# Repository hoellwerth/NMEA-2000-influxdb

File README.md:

# NMEA-2000-influxdb
An esp32 which posts traffic in the NMEA 2000 BUS to an InfluxDB 2.7 instance.

## Table of contents

- [Electrical](/Electrical): A KiCad project
- [Mechanical](/Mechanical): 3D files for casing etc.
- [Software](/Software): Platform IO Files

## Features

- [x] Listen for all known PGNs
- [x] Post data to an InfluxDB 2.7 instance
- [x] Save data to an SD-Card while offline 
- [ ] Use wifimanager

## Contribution

If you want to help with a feature or add something, just fork the repository, make your changes and open a Pull Request

## License

This project ist licensed under the [GNU GENERAL PUBLIC LICENSE](/LICENSE)

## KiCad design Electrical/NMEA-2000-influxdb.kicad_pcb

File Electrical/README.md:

# Electrical

## Table of Contents
- [Electrical](https://github.com/hoellwerth/NMEA-2000-influxdb/tree/master/Electrical#electrical)
  - [Schematic](https://github.com/hoellwerth/NMEA-2000-influxdb/blob/master/Electrical/production/schematic.pdf) The KiCad Schematic

## Components-List

A list of all the electrical components I used for the project:

- ESP32-WROOM-32E
- CAN-Transeiver SN65HVD230
- SD-Card Slot
- LM7805
- AMS1117
- BME280

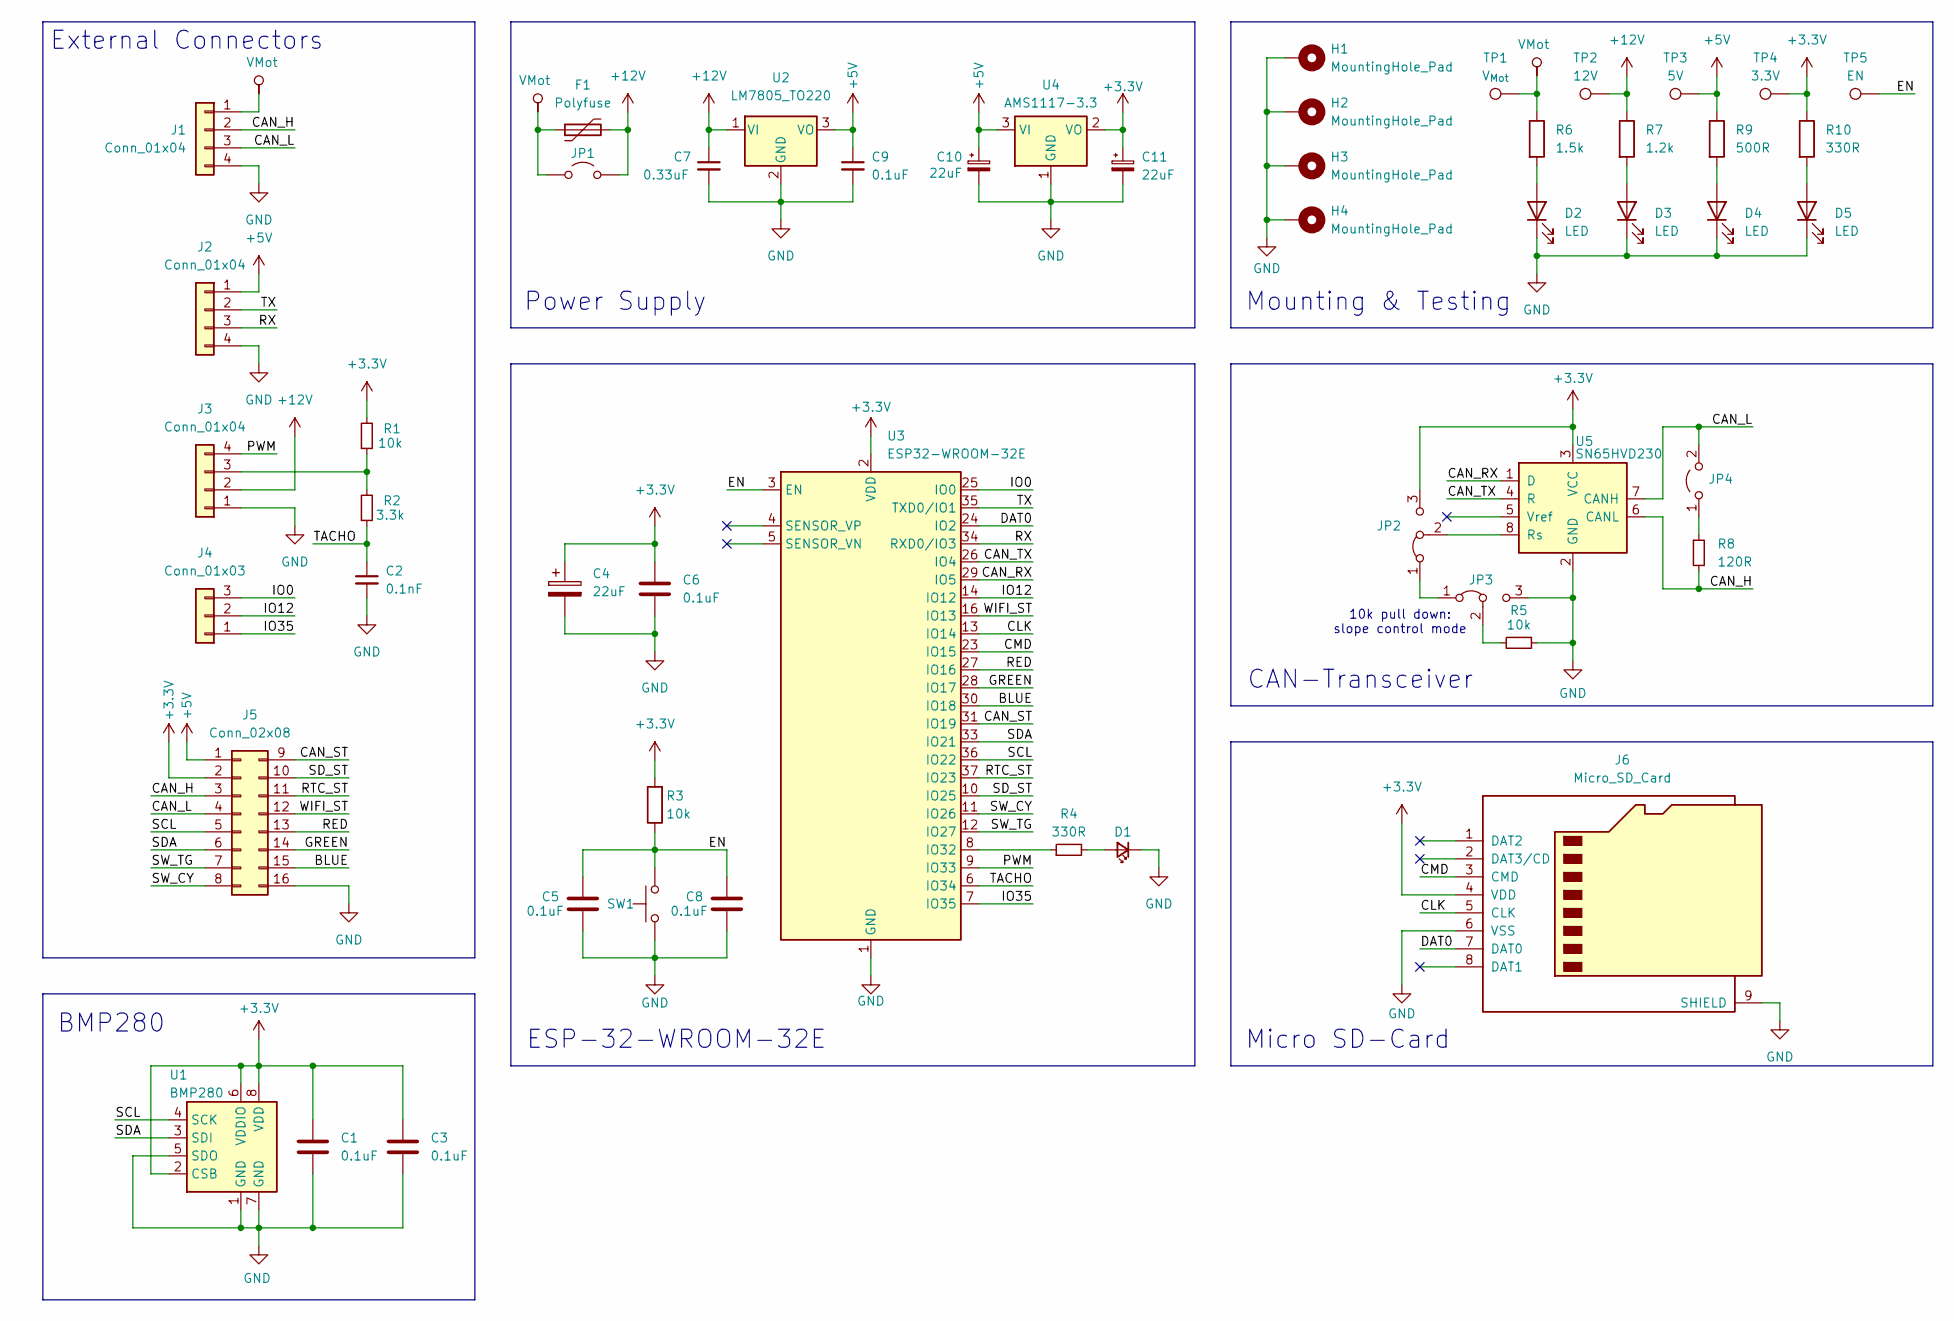
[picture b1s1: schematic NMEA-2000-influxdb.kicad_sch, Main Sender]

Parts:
C1, C3, C5, C6, C8, C9: 0.1uF; C_Disc_D5.0mm_W2.5mm_P5.00mm
C2: 0.1nF; C_Disc_D5.0mm_W2.5mm_P5.00mm
C4, C10, C11: 22uF; C_Radial_D4.0mm_H7.0mm_P1.50mm
C7: 0.33uF; C_Disc_D5.0mm_W2.5mm_P5.00mm
D1: LED_Small; LED_D3.0mm
D2, D3, D4, D5: LED; LED_D3.0mm
F1: Polyfuse; D_1210_3225Metric_Pad1.42x2.65mm_HandSolder
H1, H2, H3, H4: MountingHole_Pad; MountingHole_3mm_Pad_Via
J1: Conn_01x04; TerminalBlock_Phoenix_PT-1,5-4-5.0-H_1x04_P5.00mm_Horizontal
J2: Conn_01x04; PinSocket_1x04_P2.54mm_Horizontal
J3: Conn_01x04; FanPinHeader_1x04_P2.54mm_Vertical
J4: Conn_01x03; PinHeader_1x03_P2.54mm_Vertical
J5: Conn_02x08; IDC-Header_2x08_P2.54mm_Vertical
J6: Micro_SD_Card; microSD_HC_Hirose_DM3AT-SF-PEJM5
JP1, JP4: Jumper_2_Open; PinHeader_1x02_P2.54mm_Vertical
JP2, JP3: Jumper_3_Bridged12; PinHeader_1x03_P2.54mm_Vertical
R1, R3, R5: 10k; R_Axial_DIN0207_L6.3mm_D2.5mm_P10.16mm_Horizontal
R2: 3.3k; R_Axial_DIN0207_L6.3mm_D2.5mm_P10.16mm_Horizontal
R4, R10: 330R; R_Axial_DIN0207_L6.3mm_D2.5mm_P10.16mm_Horizontal
R6: 1.5k; R_Axial_DIN0207_L6.3mm_D2.5mm_P10.16mm_Horizontal
R7: 1.2k; R_Axial_DIN0207_L6.3mm_D2.5mm_P10.16mm_Horizontal
R8: 120R; R_Axial_DIN0207_L6.3mm_D2.5mm_P10.16mm_Horizontal
R9: 500R; R_Axial_DIN0207_L6.3mm_D2.5mm_P10.16mm_Horizontal
SW1: SW_Push; SW_PUSH_6mm
TP1: V_{Mot}; TestPoint_Pad_2.5x2.5mm
TP2: 12V; TestPoint_Pad_2.5x2.5mm
TP3: 5V; TestPoint_Pad_2.5x2.5mm
TP4: 3.3V; TestPoint_Pad_2.5x2.5mm
TP5: EN; TestPoint_Pad_2.5x2.5mm
U1: BMP280; Bosch_LGA-8_2x2.5mm_P0.65mm_ClockwisePinNumbering
U2: LM7805_TO220; TO-220-3_Vertical
U3: ESP32-WROOM-32E; ESP32-WROOM-32D
U4: AMS1117-3.3; SOT-223-3_TabPin2
U5: SN65HVD230; SOIC-8_3.9x4.9mm_P1.27mm

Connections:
+3.3V: C1.1, C3.1, C4.1, C6.1, C11.1, J5.2, J6.4 (VDD), JP2.3 (B), R1.2, R3.2, R10.1, TP4.1, U1.2 (CSB), U1.6 (VDDIO), U1.8 (VDD), U3.2 (VDD), U4.2 (VO), U5.3 (VCC)
+5V: C9.1, C10.1, J2.1, J5.1, R9.1, TP3.1, U2.3 (VO), U4.3 (VI)
+12V: C7.1, F1.2, J3.2, JP1.2 (B), R7.1, TP2.1, U2.1 (VI)
/BLUE: J5.15, U3.30 (IO18)
/CAN_H: J1.2, J5.3, R8.2, U5.6 (CANL)
/CAN_L: J1.3, J5.4, JP4.2 (B), U5.7 (CANH)
/CAN_RX: U3.29 (IO5), U5.1 (D)
/CAN_ST: J5.9, U3.31 (IO19)
/CAN_TX: U3.26 (IO4), U5.4 (R)
/CLK: J6.5 (CLK), U3.13 (IO14)
/CMD: J6.3 (CMD), U3.23 (IO15)
/DAT0: J6.7 (DAT0), U3.24 (IO2)
/EN: C5.2, C8.2, R3.1, SW1.2, TP5.1, U3.3 (EN)
/GREEN: J5.14, U3.28 (IO17)
/IO0: J4.3, U3.25 (IO0)
/IO12: J4.2, U3.14 (IO12)
/IO35: J4.1, U3.7 (IO35)
/PWM: J3.4, U3.9 (IO33)
/RED: J5.13, U3.27 (IO16)
/RTC_ST: J5.11, U3.37 (IO23)
/RX: J2.3, U3.34 (RXD0/IO3)
/SCL: J5.5, U1.4 (SCK), U3.36 (IO22)
/SDA: J5.6, U1.3 (SDI), U3.33 (IO21)
/SD_ST: J5.10, U3.10 (IO25)
/SW_CY: J5.8, U3.11 (IO26)
/SW_TG: J5.7, U3.12 (IO27)
/TACHO: C2.1, R2.1, U3.6 (IO34)
/TX: J2.2, U3.35 (TXD0/IO1)
/WIFI_ST: J5.12, U3.16 (IO13)
GND: C1.2, C2.2, C3.2, C4.2, C5.1, C6.2, C7.2, C8.1, C9.2, C10.2, C11.2, D1.1 (K), D2.1 (K), D3.1 (K), D4.1 (K), D5.1 (K), H1.1, H2.1, H3.1, H4.1, J1.4, J2.4, J3.1, J5.16, J6.6 (VSS), J6.9 (SHIELD), JP3.3 (B), R5.1, SW1.1, U1.1 (GND), U1.5 (SDO), U1.7 (GND), U2.2 (GND), U3.1 (GND), U3.15 (GND), U3.38 (GND), U3.39 (GND), U4.1 (GND), U5.2 (GND)
unnamed: D1.2 (A), R4.2
unnamed: D2.2 (A), R6.2
unnamed: D3.2 (A), R7.2
unnamed: D4.2 (A), R9.2
unnamed: D5.2 (A), R10.2
unnamed: J3.3, R1.1, R2.2
unnamed: JP2.1 (A), JP3.1 (A)
unnamed: JP2.2 (C), U5.8 (Rs)
unnamed: JP3.2 (C), R5.2
unnamed: JP4.1 (A), R8.1
unnamed: R4.1, U3.8 (IO32)
VMot: F1.1, J1.1, JP1.1 (A), R6.1, TP1.1

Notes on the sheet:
Power Supply
CAN-Transceiver
Mounting & Testing
ESP-32-WROOM-32E
10k pull down: slope control mode
Micro SD-Card
BMP280
External Connectors

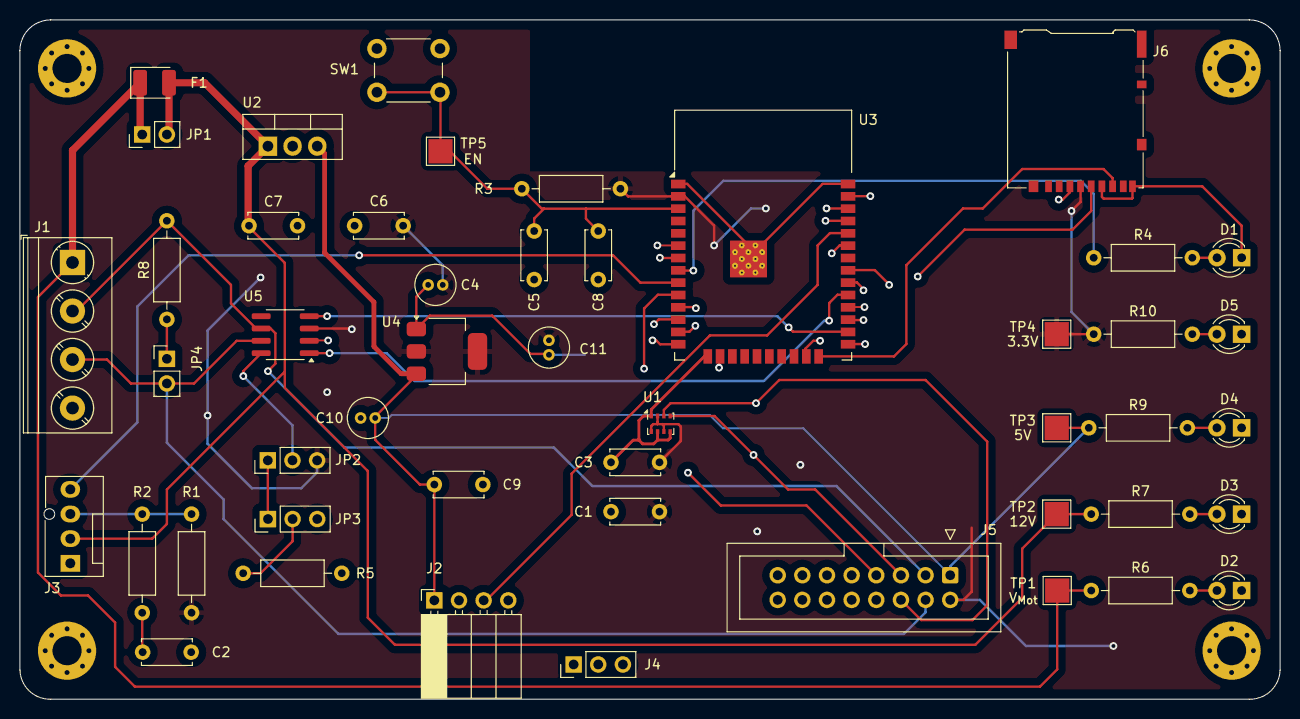
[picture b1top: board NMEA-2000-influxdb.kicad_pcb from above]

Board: 4 copper layers, 129.9 x 70.0 mm, 52 parts (0 on the bottom side), 42 nets.

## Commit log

2023-05-15 Added Arduino script
2023-05-15 Added KiCad Project
2023-05-15 Added KiCad Schematic
2023-05-15 Added KiCad PCB
2023-05-20 Added InfluxDB Write
2023-06-04 Added Receiver
2023-06-04 Updated Receiver
2023-06-04 Changed too much
2023-06-05 Added BatterHandler
2023-06-06 Updated connection validation
2023-06-06 Added TymeSync
2023-06-06 Added connectWifi
2023-06-08 Added Voltage to Influx
2023-06-09 Added Current and Temp to Influx
2023-06-09 Added handleFluidTanks
2023-06-11 Updated KiCad Project
2023-06-11 Updated KiCad Schematic
2023-06-12 Moved KiCad project into 'Electrical' Folder
2023-06-12 Moved main sketch into Software FOlder
2023-06-12 Moved Receiver into 'Software/Receiver' folder
2023-06-12 Moved listener into 'Software/Listener' folder
2023-06-12 Moved main sketch into sperat folder
2023-06-12 Added 'Mechanical' fodler
2023-06-13 Rename .github/workflow.yml to .github/workflows/main.yml
2023-06-13 Create LICENSE
2023-06-15 Cleaned up code
2023-06-16 Added client side timestamps
    Enablef client side influxdb timestamps - set time precision to milliseconds
2023-06-16 cleaned code
2023-06-17 Added File System commands
2023-06-17 Added exmaple.json
2023-06-20 Rename main.yml to compile.yml
2023-06-22 Added Writing to log.txt
2023-06-24 Fixed calling of writeFromBuffer
2023-06-24 Removed debug print of wifi status
2023-06-26 Prepared merge
2023-06-26 'Merged'
2023-06-26 Added 'Software/Readme.md'
2023-06-26 Added Table of contents in 'Software/README.md'
2023-06-26 Added Introduction in 'Software/README.md'
2023-06-26 Added Usage in 'Software/README.md'
2023-06-26 Added Libraries in 'Software/README.md'
2023-07-07 Updated sdCard
2023-07-12 Added Example File structure
2023-07-12 Changed File type to '.txt'
2023-07-12 Removed Subfolder granulty
2023-07-12 Added writeToBuffer function
2023-07-13 Finished writeToBuffer function
2023-07-13 Updated setupSD()
2023-07-13 Added queue
2023-07-16 Added Symbol
2023-07-16 Added SN65HVD230 Module to schematic
2023-07-16 Added RTC-Module Symbol
2023-07-16 Added RTC-Module to schematic
2023-07-16 Added BMP280-Module Symbol
2023-07-16 Added BMP280-Module
2023-07-16 Added SD-Card-Module
2023-07-16 Added SD-Card-Module to Schematic
2023-07-18 Added Power Connector
2023-07-18 Added esp32 Footprint
2023-07-21 Added DS3231 Library
2023-07-21 Added Wire Library
2023-07-22 Removed BMP280 Sensor
2023-07-26 Added RTC Module
2023-07-26 Updated Dependecies
2023-08-20 Added mainBattery to flushBuffer
2023-09-02 Outsource buffer
2023-11-21 Replaced SN65HVD230-Module with SN65HVD230
2023-11-23 Added external connectors
2023-11-23 Added board
2023-11-26 Updated board and added heatsink
2023-12-12 Added .gitignore
2023-12-12 Added Seven segment displays
2023-12-12 Added Alphanumeric display
2023-12-16 Added I2C adresses
2024-01-02 Added Display PCB
2024-01-03 Updated Display
2024-03-16 Updated schematic
2024-03-18 Updated domain entries
2024-03-20 Added Mainboard
2024-04-06 Removed RTC-Module
2024-04-06 Added Backup CAN Transceiver Module Switched Push Button for SPST Switch Added Heatsink for LM7805
2024-04-06 Added VMOT Added Power LEDs
2024-04-06 Updated SN65HVD Module
2024-05-02 Cleared up project
2024-05-04 Cleared up Schematic
2024-05-04 Updated PCB
2024-05-04 Updated Project
2024-05-12 Added 3D Models
2024-05-12 Added SMD SD-Card
2024-05-14 Updated 3d Models and PCB
2024-05-14 Deleted debricated Project
2024-05-17 Finished Revision 3
2024-05-23 Finished Schematic Rev 4
2024-05-29 Finished Rev 4 Schematics
2024-05-29 Added Schematic PDF
2024-06-12 Finished Rev 4
2024-06-22 Adde diBom
